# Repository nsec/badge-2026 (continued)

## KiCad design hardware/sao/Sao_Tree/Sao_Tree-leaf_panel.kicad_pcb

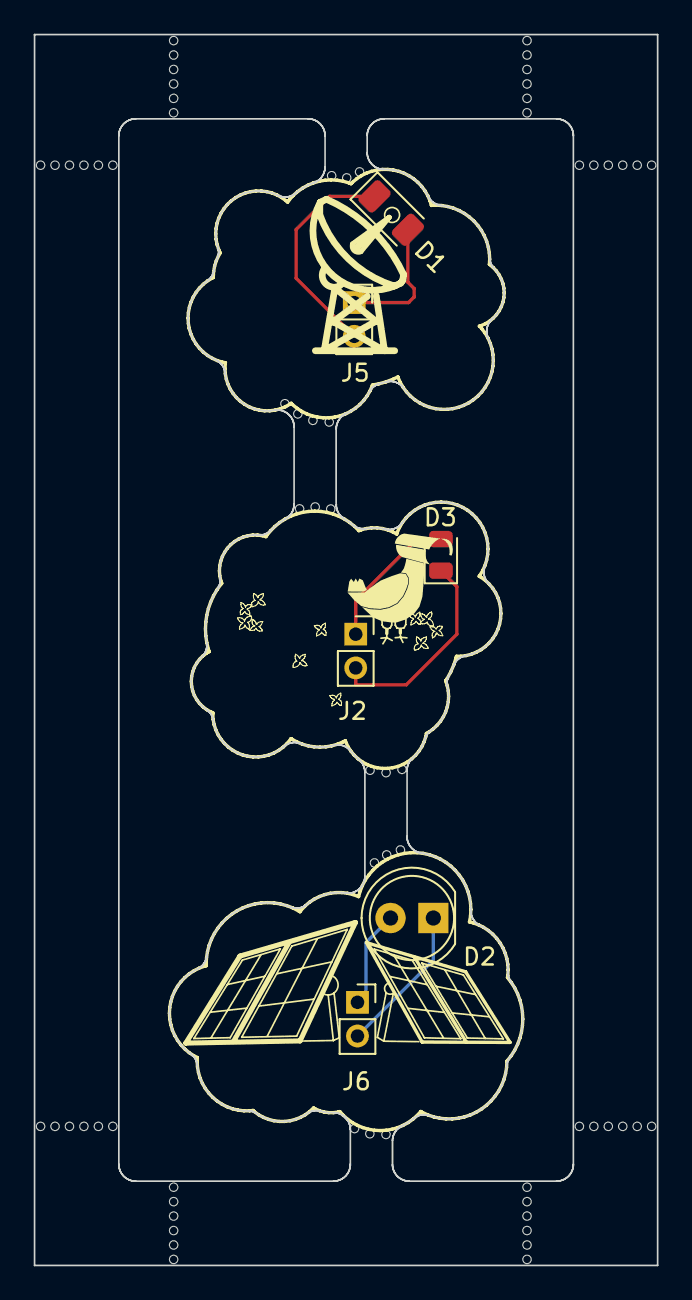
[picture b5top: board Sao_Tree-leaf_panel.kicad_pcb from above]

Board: 2 copper layers, 37.0 x 73.0 mm, 73 parts (0 on the bottom side), 6 nets.

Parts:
D1: LED; LED_1206_3216Metric
D2: LED; LED_D5.0mm
D3: LED; LED_0805_2012Metric
J2, J5, J6: Conn_01x02_Socket; PinSocket_1x02_P2.00mm_Vertical
KiKit_MB_1_2, KiKit_MB_1_3, KiKit_MB_1_4, KiKit_MB_1_5, KiKit_MB_1_6, KiKit_MB_1_7, KiKit_MB_2_2, KiKit_MB_2_3, KiKit_MB_2_4, KiKit_MB_2_5, KiKit_MB_2_6, KiKit_MB_2_7, KiKit_MB_3_2, KiKit_MB_3_3, KiKit_MB_3_4, KiKit_MB_3_5, KiKit_MB_3_6, KiKit_MB_3_7, KiKit_MB_4_2, KiKit_MB_4_3, KiKit_MB_4_4, KiKit_MB_4_5, KiKit_MB_4_6, KiKit_MB_4_7, KiKit_MB_5_2, KiKit_MB_5_3, KiKit_MB_5_4, KiKit_MB_5_5, KiKit_MB_5_6, KiKit_MB_5_7, KiKit_MB_6_2, KiKit_MB_6_3, KiKit_MB_6_4, KiKit_MB_6_5, KiKit_MB_6_6, KiKit_MB_6_7, KiKit_MB_7_2, KiKit_MB_7_3, KiKit_MB_7_4, KiKit_MB_7_5, KiKit_MB_7_6, KiKit_MB_7_7, KiKit_MB_8_2, KiKit_MB_8_3, KiKit_MB_8_4, KiKit_MB_8_5, KiKit_MB_8_6, KiKit_MB_8_7, KiKit_MB_9_2, KiKit_MB_9_3, KiKit_MB_9_4, KiKit_MB_10_2, KiKit_MB_10_3, KiKit_MB_10_4, KiKit_MB_10_5, KiKit_MB_11_2, KiKit_MB_11_3, KiKit_MB_11_4, KiKit_MB_12_2, KiKit_MB_12_3, KiKit_MB_12_4, KiKit_MB_13_3, KiKit_MB_13_4, KiKit_MB_13_5, KiKit_MB_14_2, KiKit_MB_14_3, KiKit_MB_14_4: NPTH

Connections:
Board_0-+3.3V: D1.2 (A), J5.1
Board_0-GND: D1.1 (K), J5.2
Board_1-+3.3V: D3.2 (A), J2.1
Board_1-GND: D3.1 (K), J2.2
Board_2-+3.3V: D2.2 (A), J6.1
Board_2-GND: D2.1 (K), J6.2

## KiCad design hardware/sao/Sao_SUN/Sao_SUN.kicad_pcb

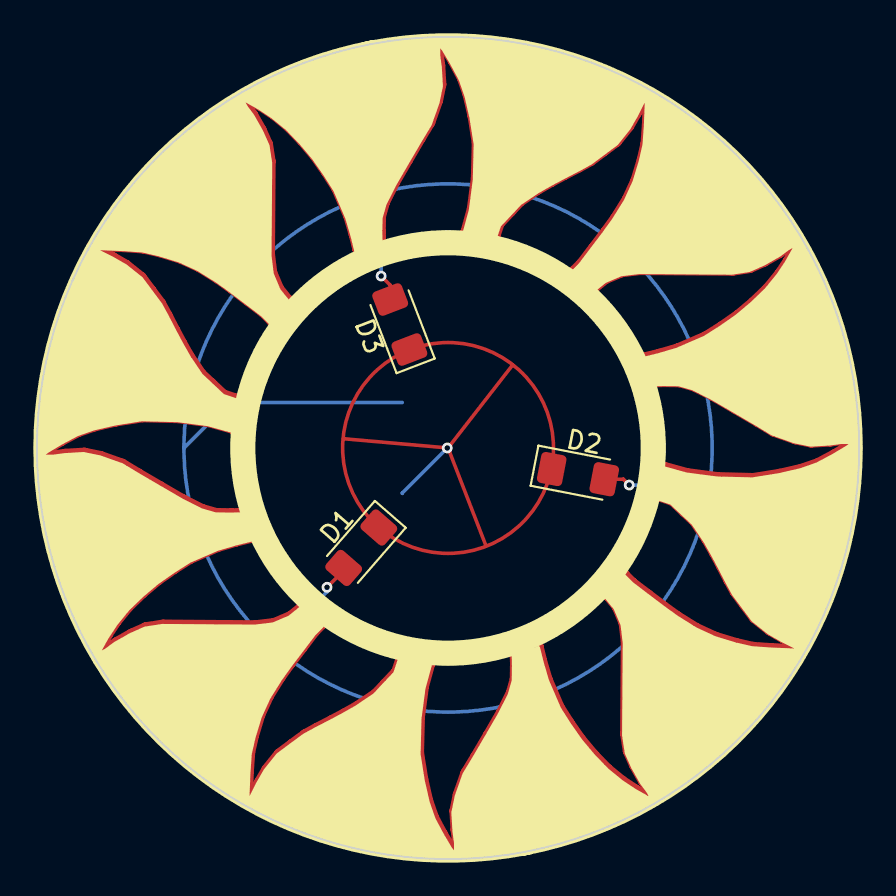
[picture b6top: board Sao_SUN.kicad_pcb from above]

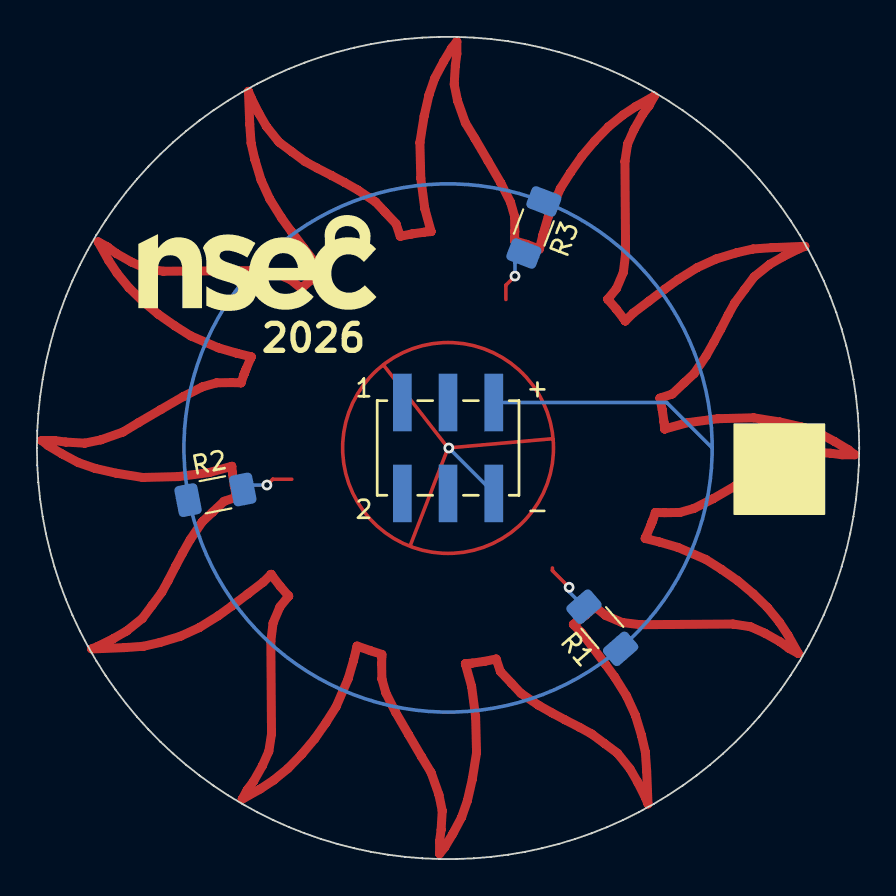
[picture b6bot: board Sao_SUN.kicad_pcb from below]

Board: 2 copper layers, 45.7 x 45.7 mm, 7 parts (4 on the bottom side), 5 nets.

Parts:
D1, D2, D3: LED; LED_1206_3216Metric_Pad1.42x1.75mm_HandSolder
J1: SAO Connector SMD
R1, R2, R3: 330; R_1206_3216Metric_Pad1.30x1.75mm_HandSolder

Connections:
+3.3V: J1.5 (3V3), R1.1, R2.1, R3.1
GND: D1.1 (K), D2.1 (K), D3.1 (K), J1.6 (GND)
unnamed: D1.2 (A), R1.2
unnamed: D2.2 (A), R2.2
unnamed: D3.2 (A), R3.2

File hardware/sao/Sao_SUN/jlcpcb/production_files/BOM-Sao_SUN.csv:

Comment,Designator,Footprint,LCSC,Quantity
LED,D2,LED_1206_3216Metric_Pad1.42x1.75mm_HandSolder,,1
LED,D3,LED_1206_3216Metric_Pad1.42x1.75mm_HandSolder,,1
LED,D1,LED_1206_3216Metric_Pad1.42x1.75mm_HandSolder,,1
330,R1,R_1206_3216Metric_Pad1.30x1.75mm_HandSolder,,1
330,R2,R_1206_3216Metric_Pad1.30x1.75mm_HandSolder,,1
SAO Connector SMD,J1,SAO Connector SMD,,1
330,R3,R_1206_3216Metric_Pad1.30x1.75mm_HandSolder,,1

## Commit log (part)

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2025-12-01 Updated README
    Updated the README to add layout for hardware, firmware, and credits' sections.
2025-12-14 Initial scaffold in place
2025-12-23 Add base ICS challenge with MQTT and Wifi
2026-01-03 Add gitgnore for SSID creds
2026-01-05 Change SSID creds to secrets.h and port MQTT client to TLS
2026-02-08 sub-component hardware
2026-02-16 Functionality included
2026-02-18 Working button integration and test commands
2026-02-22 cli: use std::string instead of Arduino String
    Replace Arduino's String class with std::string throughout the CLI
    module and its users. This change prepares the codebase for
    cross-platform compilation by removing the dependency on Arduino's
    WString implementation.
    Changes:
    - Update CommandHandler typedef to use std::string
2026-02-22 doc: add native simulator instructions to README
    Document how to build and run the native/desktop simulator:
    - Submodule initialization for FreeRTOS-Kernel
    - Build command (pio run -e native)
    - Run command and Ctrl+C to exit
2026-02-22 build: add native simulator environment with FreeRTOS POSIX port
    Add a PlatformIO native build environment that allows the badge firmware
    to run on a desktop machine. The simulator uses the FreeRTOS POSIX port
    to provide real task scheduling via pthreads.
    FreeRTOS integration:
    - Add FreeRTOS-Kernel as a git submodule (extern/FreeRTOS-Kernel)
    - Add FreeRTOSConfig.h configured for the POSIX/Linux port
2026-02-22 changing structure
2026-03-01 tasks: add controller and CLI tasks
    Define ControllerTask (dispatches ControllerEvents, orchestrates LED
    test sequence via LedCommand queue, sends CliResponse on completion)
    and CliTask (wraps cli::poll() in a FreeRTOS task loop). Task classes
    are defined but not yet instantiated.
2026-03-01 led: extract animations into LED task module
    Move animation implementations (solidColor, pixelWalk, rainbow, off)
    from cli.cpp into led_task.h/cpp. The CLI's cmdLedTest() now calls
    these functions directly and uses animationName() for progress output.
    LedTask::run() dispatches LedCommands to the same animation functions.
2026-03-01 simulator: start FreeRTOS scheduler instead of calling loop()
    The main thread is not a FreeRTOS-managed thread, so calling loop()
    which does vTaskDelay() triggers a configASSERT failure. Start the
    scheduler after setup() and let it run the tasks directly, matching
    how Arduino/ESP32 works under the hood.
    Also enable debug builds (-O0 -g3) for the native environment.
2026-03-01 simulator: fix native build errors
    Add printf() to the simulator Print class to match the Arduino API
    available on ESP32.
    Fix vAssertCalled linkage in FreeRTOSConfig.h by adding extern "C" for
    C++ translation units, resolving undefined reference at link time.
2026-03-01 tasks: activate heartbeat timer
    Replace the manual heartbeat toggle in loop() with the FreeRTOS
    software timer (core::heartbeatStart()) called from setup().
    I didn't see a ~500ms blinking LED on the badge before my
    changes, so I'm assuming the core::hw::statusLedSet function
    may not be doing the right thing at the moment.
2026-03-01 Add a .clang-format that approximates the current coding style
2026-03-01 Updated centralized hwid functionality
2026-03-01 Additional shuffle bytes for xor/nonce
2026-03-01 moar lint plz
2026-03-06 Suggestions implemented :bow:
2026-03-06 initial test of nfc capabilities
2026-03-07 refactor changes with mifaire+. emulation still not super stable
2026-03-07 updating so badge emulates it's hwid for social purposes
2026-03-08 linnnnnntttttttt
2026-03-08 added clear command
2026-03-08 docs: add CLAUDE.md with project conventions and build instructions
2026-03-09 fix: reset badges via DTR toggle before pairing test
2026-03-13 all generic button and interactions updated and working better
2026-03-13 unique nvs tracking
2026-03-18 fixing serial prints and small visual cleanup
2026-03-18 linterrrr
2026-03-22 quantum crystal challenge code-complete (pre-difficulty tuning)
2026-03-24 linterrrrrrr
2026-03-24 Story wise addition and fine tuning
2026-03-24 lint lint lint - I need to do the hook to stop this
2026-03-29 addresing comments
2026-04-05 cleaning up old dock folder
2026-04-14 feat: display NorthSec logo on e-ink at boot
    Add PROGMEM bitmap converted from nsec_200x200_bw_ordered.bmp and
    draw it using GxEPD2 paged drawInvertedBitmap on startup (rotation 1).
2026-04-14 feat: add GxEPD2 e-ink display driver (GDEH0154D67 200x200)
    Integrate 1.54" BW e-ink display sharing HSPI bus with NFC ST25R3916.
    Pins: CS=IO41, DC=IO42, RST=IO45, BUSY=IO46. Adds einktest CLI command.
2026-04-14 feat: add bmp2header.sh tool for e-ink bitmap conversion
    Converts BMP/PNG images to GxEPD2-compatible 1-bit PROGMEM C headers
    using ImageMagick and xxd. Includes byte count verification.
2026-04-14 feat: dynamic e-ink display with NFC status, social progress, and auto-revert
    - DisplayTask with command queue shows mode changes, scan results, pair
    outcomes, and social progress with per-event timeouts (5-15s)
    - Graceful missing-display detection via SSD1681 soft-reset + BUSY pin
    - Controller tracks NFC mode for toggle behavior; always updates display
    on button press to prevent stale screens
    - NFC task sends scan UIDs and pair results to display queue
2026-04-15 updating bus sharing between light and dock
2026-04-19 Initial triple firmware scaffold and flashing process
2026-04-24 challenges: Add the mystery string challenge
    The purpose of the challenge is to explore different encoding modes on a
    serial bus.
    The intended solution involves some soldering to test points and
    capturing the serial output, but extracting the string blob through
    reverse engineering is a possible alternative.
    The analysis and decoding of the string should be the same regardless
2026-04-24 challenges: Cleartext flag in firmware
    Including a simple cleartext flag as a reward for successfully dumping
    the badge firmware for those who are doing hardware hacking for the
    first time.
2026-04-24 Light tweak, eink message tweak, and quantum adjustements based on qa
2026-04-24 adding buildfs step
2026-04-25 Add nlohmann-json to the dependencies
2026-04-25 portal: constrain viewport to the contents on mobile
    Without the viewport specification, the page starts too
    zoomed-out (on iOS at least). Don't allow horizontal scrolling.
2026-04-25 portal: draw spores using canvas
    The performance of the original DOM-based animation was
    atrocious on mobile (or at least, it made my phone really hot
    and made card expansions choppy).
    They are re-implemented and tweaked a bit to use a "canvas"
    element.
2026-04-25 controller: integrate WiFi portal with task/queue architecture
    - Add PortalToggleRequest and ConfigChangedEvent to ControllerEvent
    - Controller handles portal start/stop via PortalCommand queue
    - Controller shows the selected color on save
    - main.cpp creates portal queue/task, inits config NVS, and applies
    saved brightness on boot
    - Add portal queue depth and task priority to badge_config
2026-04-25 cli: add wifitest command to toggle WiFi config portal
2026-04-25 portal: clean-up stale style rules
2026-04-25 network: add WiFi AP portal task with captive portal and REST API
    PortalTask runs a SoftAP (SSID: NSEC-XXXX based on MAC), a DNS
    server for captive portal redirect, and an ESPAsyncWebServer serving
    a config page. REST endpoints:
    GET /api/config — current user config
    GET /api/social — social progress
    POST /api/config — save name, color, brightness
2026-04-25 tools: add dev server for testing portal on mobile
    Serves portal.html with static API responses for config and social
    endpoints, useful for iterating on the UI from a phone.
2026-04-25 portal: attempt at implementing NFC wifi access
    UNTESTED; need to fix my badge's antennae.
2026-04-25 storage: add NVS contact profile storage and CLI commands
    Add nvs_contacts module that stores contact profiles (name, pronouns,
    affiliation, contact, color) as a packed binary blob in NVS, keyed by
    MAC address. Field size limits are defined in badge_config.h to match
    the NFC-DEP single-frame constraint (~210 bytes available).
    CLI commands for testing: contactadd, contactlist, contactdel.
2026-04-25 style: fix #define indentation in nfc_task.cpp
2026-04-25 portal: WPA2-protect the portal with NVS-persisted credentials
    Replace the open WiFi AP with a WPA2-PSK protected one. On first portal
    activation, the controller task generates a unique SSID (NSEC-XXYYZZ
    from the last 3 MAC bytes) and a random 10-character alphanumeric
    passphrase using the hardware TRNG (esp_random with
    bootloader_random_enable for true entropy before WiFi is active).
    Credentials are persisted in NVS and reused across reboots.
2026-04-25 feat: map UP button to toggle WiFi config portal
2026-04-25 Build fix: add missing wifi portal deps to conference-only environment
2026-04-25 animation: add LED animation descriptions
    Adds JSON animation definitions for the badge's LED engine:
    boot, smooth_glow, rainbow, splotches, cycles, burning, flow,
    gold_calm, pink_gold_circling, wifi_portal, and three favorite-color
    variants (fav_orbs, fav_breathe, fav_noise).
2026-04-25 animations: adjust boot animation timing
2026-04-25 Fix: wonky serial input echo due to race condition
2026-04-25 feat: play wifi_portal animation during portal and support live palette updates
    Start the wifi_portal LED animation when the WiFi portal is activated and
    turn it off when the portal shuts down. Add a PaletteUpdate LED command so
    that changing the user's favorite color via the portal updates the running
    animation in real time. Fix resolvePalette to accept RGB directly so
    achromatic colors like white are no longer mapped to red.
2026-04-25 animation: coding style fixes
2026-04-25 refactor: centralize NFC LED control in the controller
    NfcTask no longer pokes the LED queue. Mode start/stop colours
    (white/cyan/orange/off) are now set by ControllerTask alongside the
    NfcCommand it issues, and async results (scan complete, pair outcome)
    are sent back as new ControllerEvent variants (NfcScanResultEvent and
    NfcPairResultEvent) which the controller turns into ProgressFlash
    commands.
2026-04-25 animation: render solid colours as a soft per-LED breathe
    All Solid* commands (SolidRed/Green/Blue/White/Orange/Cyan and SolidColor)
    now go through a buildSolidBreathe(color) animation instead of
    rgbSetAll + delay(1000).
    Each command builds an 18-track AnimationDef with one static-position
    light per LED, a tight radius, and a Breathe intensity (0.6..1.0 over
    2.5s). Per-LED phase offsets stepped by 2π·(1−1/φ) keep the LEDs out of
2026-04-25 Code format fix
2026-04-25 portal: remove mentions of attraction
2026-04-25 testing changing only if changed in embed html
2026-04-25 animations: add ping-pong animation
2026-04-25 updated mkspiffs
2026-05-03 nfc: advertise nsec.io/badge URL when idle
    Adds NfcMode::UrlEmulator which programs the NTAG213 emulator with an
    NDEF URI record. ControllerTask starts it on enterIdle() and tears it
    down via cleanupCurrent(), so phones tapping an idle badge get a
    clickable https://nsec.io/badge prompt.
2026-05-04 feat: add SAO designs (Sun, Tree, Robotplant)
    Three SAO (Shitty Add-On) KiCad projects with JLCPCB production files
    and panelization scripts.
2026-05-07 DRM obfuscation features
2026-05-07 artifact file removal
2026-05-11 Add broker code and command to publish mqtt messages from the badge cli
2026-05-12 fix mqtt_pub creds
2026-05-12 fix ipv6 --> ipv4 for broker and publish to broker-system
